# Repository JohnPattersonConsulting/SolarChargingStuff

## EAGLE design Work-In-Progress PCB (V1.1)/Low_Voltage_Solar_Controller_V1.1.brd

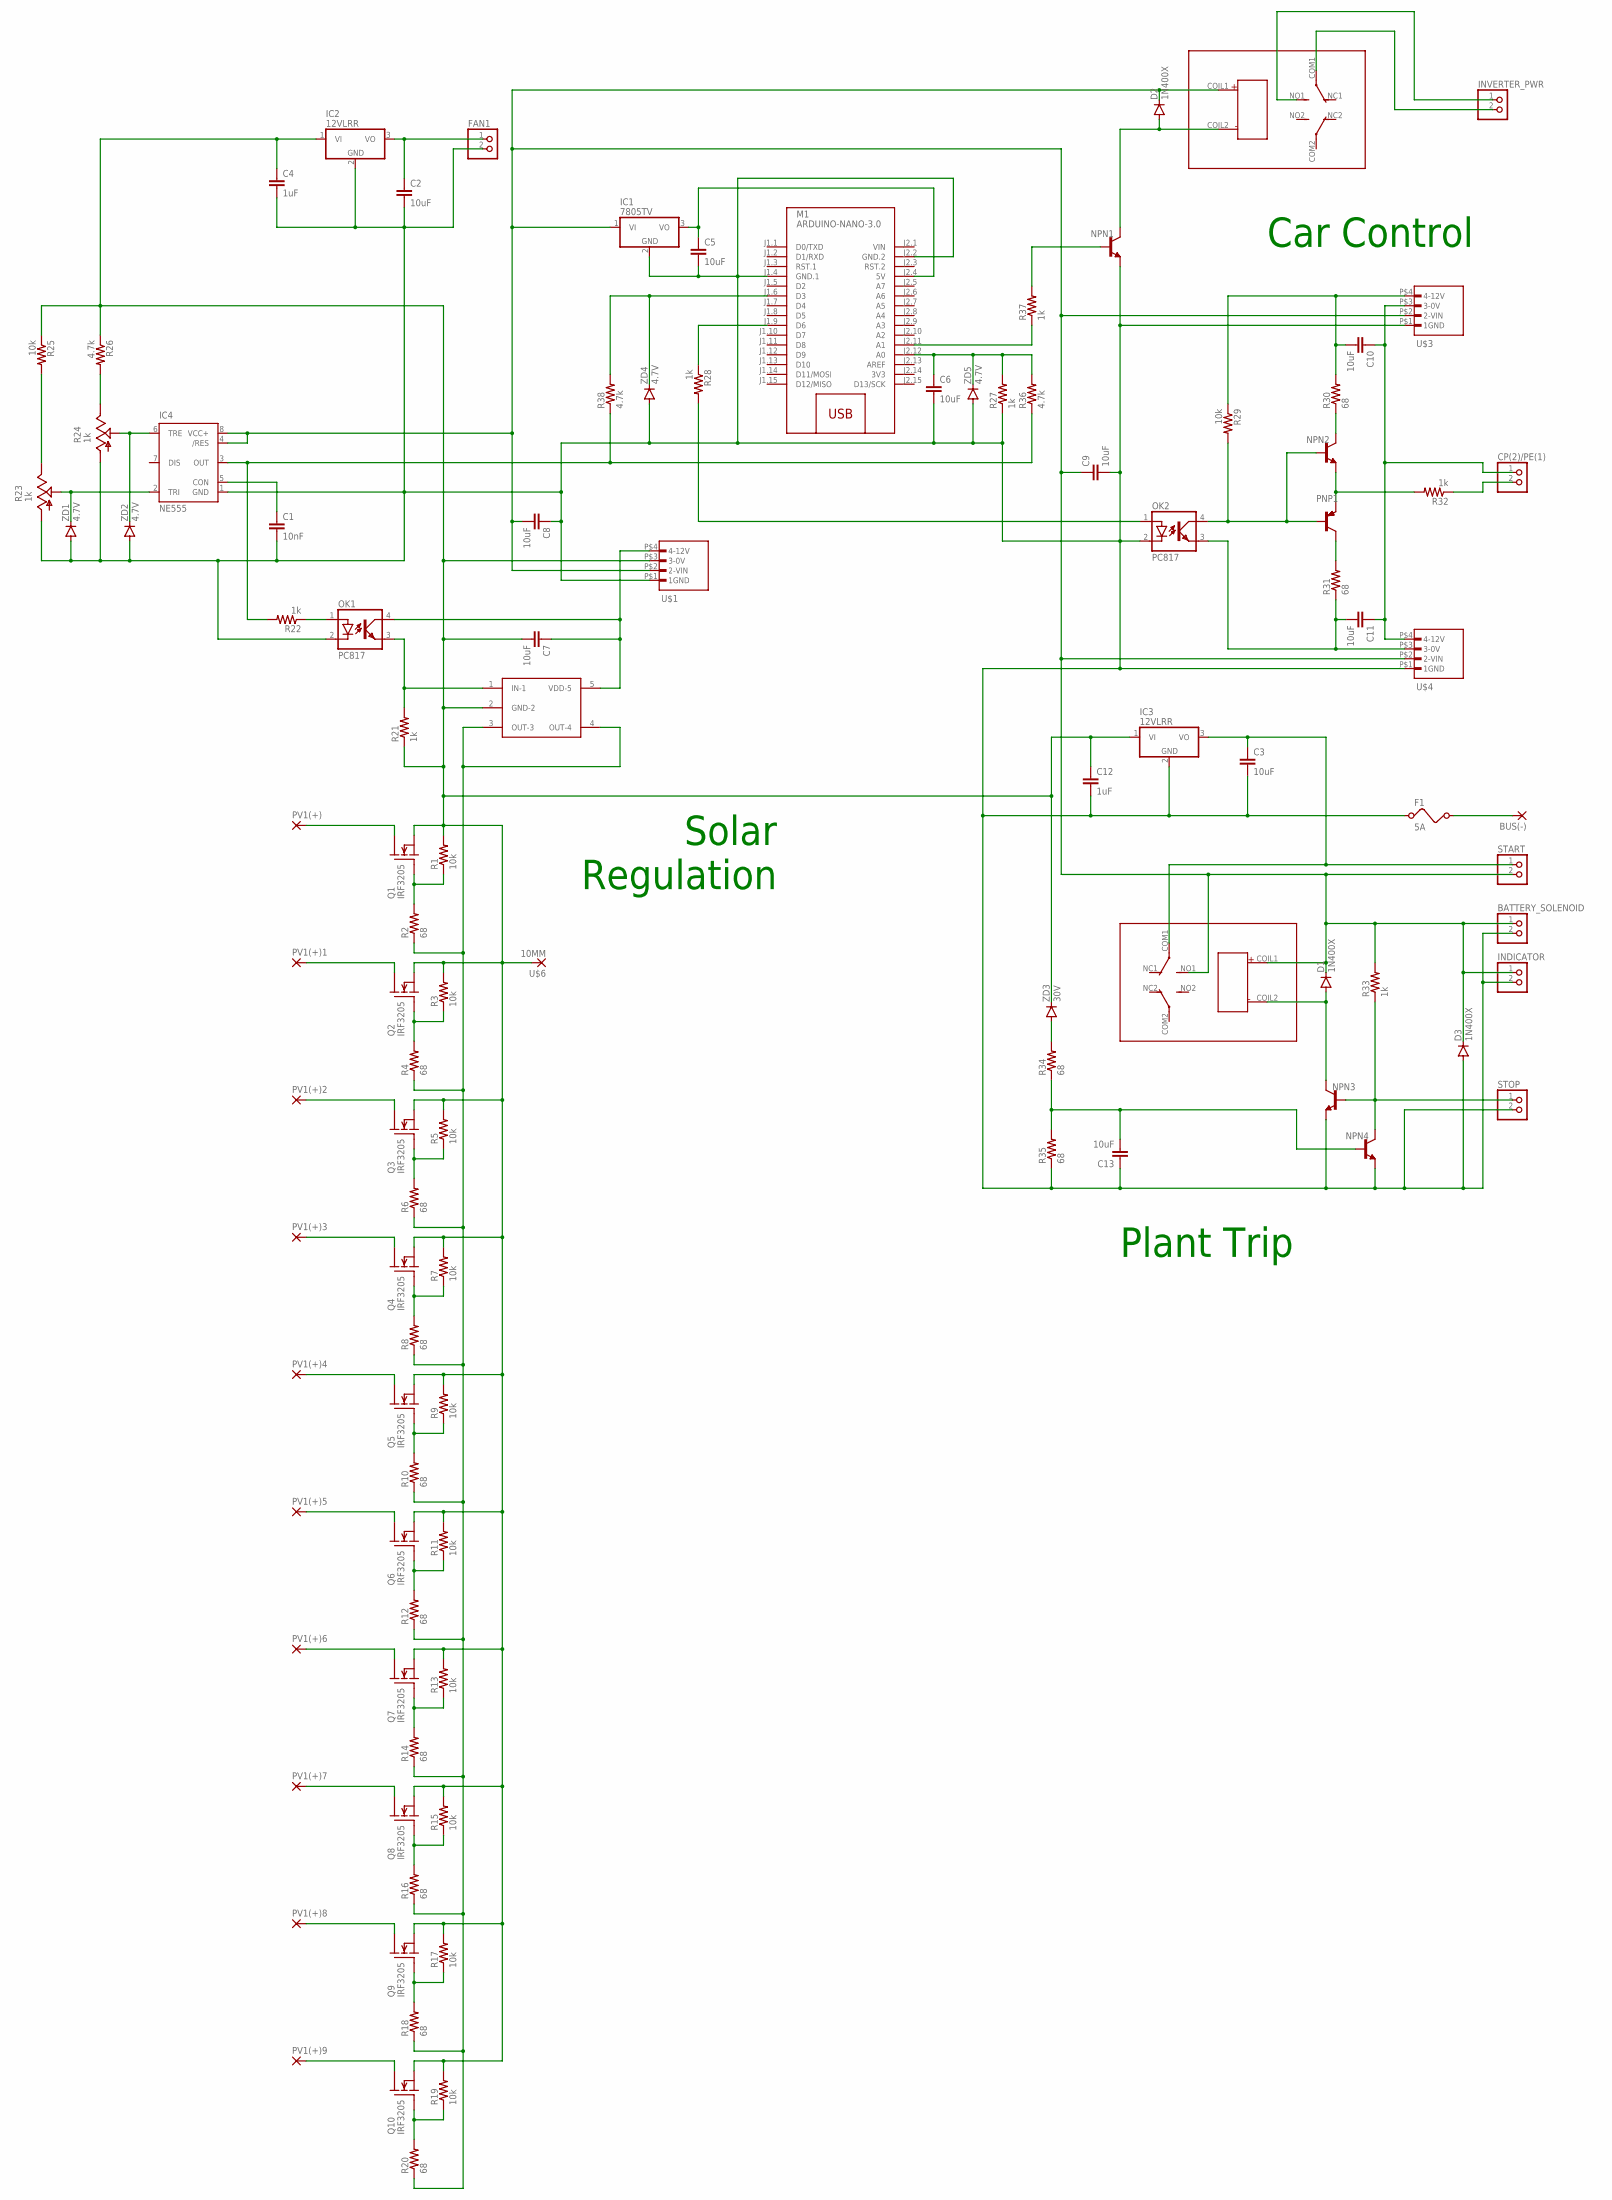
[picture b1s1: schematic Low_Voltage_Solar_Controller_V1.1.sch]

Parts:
BATTERY_SOLENOID: PINHD-1X2; 1X02
BUS(-): 5MM_PAD; 5MM
C1: 10nF; C0603
C2, C3, C5, C6, C7, C8, C9, C10, C11, C13: 10uF; C0805
C4, C12: 1uF; C0805
CP(2)/PE(1): PINHD-1X2; 1X02
D1, D2, D3: 1N400X; DO41-10
F1: 5A; FUSE_HOLDER
FAN1: PINHD-1X2; 1X02
IC1: 7805TV; TO220V
IC2, IC3: 12VLRR; TO220V
IC4: NE555; DIL-08
INDICATOR: PINHD-1X2; 1X02
INVERTER_PWR: PINHD-1X2; 1X02
M1: ARDUINO-NANO-3.0
NPN1, NPN2, NPN3, NPN4: -NPN-TO92-EBC; TO92-EBC
OK1, OK2: PC817; DIL04
PNP1: BCX58-PNP-TO92-EBC; TO92-EBC
PV1(+), PV1(+)1, PV1(+)2, PV1(+)3, PV1(+)4, PV1(+)5, PV1(+)6, PV1(+)7, PV1(+)8, PV1(+)9: 5MM_PAD; 5MM
Q1, Q2, Q3, Q4, Q5, Q6, Q7, Q8, Q9, Q10: IRF3205; TO220
R1, R3, R5, R7, R9, R11, R13, R15, R17, R19, R25, R29: 10k; R0805
R2, R4, R6, R8, R10, R12, R14, R16, R18, R20, R30, R31, R34, R35: 68; R0805
R21, R22, R27, R28, R32, R33, R37: 1k; R0805
R23, R24: 1k; RJ9W
R26, R36, R38: 4.7k; R0805
START: PINHD-1X2; 1X02
STOP: PINHD-1X2; 1X02
U$1, U$3, U$4: IB0512S-W75R3
U$2: NCP51100; SOT23-5
U$5, U$8: J104D2C12VDC.20S
U$6: 10MM
ZD1, ZD2, ZD4, ZD5: 4.7V; SOD-123_MINI-SMA
ZD3: 30V; DO214AA

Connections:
3V3: M1.J2.14 (3V3)
unnamed: PV1(+).P$1, Q1.2 (D)
unnamed: C4.1, C7.2, C12.1, IC2.1 (VI), IC3.1 (VI), Q1.3 (S), Q2.3 (S), Q3.3 (S), Q4.3 (S), Q5.3 (S), Q6.3 (S), Q7.3 (S), Q8.3 (S), Q9.3 (S), Q10.3 (S), R1.2, R3.2, R5.2, R7.2, R9.2, R11.2, R13.2, R15.2, R17.2, R19.2, R21.1, R25.1, R26.1, U$1.P$3 (3-0V), U$2.2 (GND-2), U$6.P$1, ZD3.C
unnamed: Q1.1 (G), R1.1, R2.2
unnamed: PV1(+)1.P$1, Q2.2 (D)
unnamed: M1.J1.6 (D3), R38.2, ZD4.C
unnamed: Q2.1 (G), R3.1, R4.2
unnamed: PV1(+)2.P$1, Q3.2 (D)
unnamed: Q3.1 (G), R5.1, R6.2
unnamed: PV1(+)3.P$1, Q4.2 (D)
unnamed: C5.1, IC1.3 (VO), M1.J2.4 (5V)
unnamed: Q4.1 (G), R7.1, R8.2
unnamed: PV1(+)4.P$1, Q5.2 (D)
unnamed: Q5.1 (G), R9.1, R10.2
unnamed: PV1(+)5.P$1, Q6.2 (D)
unnamed: Q6.1 (G), R11.1, R12.2
unnamed: PV1(+)6.P$1, Q7.2 (D)
unnamed: Q7.1 (G), R13.1, R14.2
unnamed: PV1(+)7.P$1, Q8.2 (D)
unnamed: Q8.1 (G), R15.1, R16.2
unnamed: PV1(+)8.P$1, Q9.2 (D)
unnamed: Q9.1 (G), R17.1, R18.2
unnamed: PV1(+)9.P$1, Q10.2 (D)
unnamed: Q10.1 (G), R19.1, R20.2
unnamed: R2.1, R4.1, R6.1, R8.1, R10.1, R12.1, R14.1, R16.1, R18.1, R20.1, U$2.3 (OUT-3), U$2.4 (OUT-4)
unnamed: OK1.3 (EMIT), R21.2, U$2.1 (IN-1)
unnamed: C7.1, OK1.4 (COL), U$1.P$4 (4-12V), U$2.5 (VDD-5)
unnamed: BATTERY_SOLENOID.1, C8.2, C9.1, D1.C, D2.C, D3.C, IC1.1 (VI), IC4.4 (/RES), IC4.8 (VCC+), INDICATOR.1, R33.2, START.2, U$1.P$2 (2-VIN), U$3.P$2 (2-VIN), U$4.P$2 (2-VIN), U$5.COIL1, U$8.COIL1, U$8.NO1
unnamed: OK1.1 (A), R22.1
unnamed: BATTERY_SOLENOID.2, C1.2, C2.2, C3.2, C4.2, C5.2, C6.2, C8.1, C9.2, C12.2, C13.1, D3.A, F1.P$1 (1), F1.P$2 (1), FAN1.2, IC1.2 (GND), IC2.2 (GND), IC3.2 (GND), IC4.1 (GND), INDICATOR.2, M1.J1.4 (GND.1), M1.J2.2 (GND.2), NPN1.E, NPN3.E, NPN4.E, OK1.2 (C), OK2.2 (C), R23.A, R24.A, R27.1, R35.1, STOP.2, U$1.P$1 (1GND), U$3.P$1 (1GND), U$4.P$1 (1GND), ZD1.A, ZD2.A, ZD4.A, ZD5.A
unnamed: C1.1, IC4.5 (CON)
unnamed: C2.1, FAN1.1, IC2.3 (VO)
unnamed: IC4.6 (TRE), R24.S, ZD2.C
unnamed: IC4.2 (TRI), R23.S, ZD1.C
unnamed: R23.E, R25.2
unnamed: R24.E, R26.2
unnamed: C6.1, M1.J2.12 (A0), R27.2, R36.2, ZD5.C
unnamed: M1.J1.9 (D6), R28.1
unnamed: OK2.1 (A), R28.2
unnamed: NPN2.B, OK2.4 (COL), PNP1.B, R29.2
unnamed: C10.1, C11.1, CP(2)/PE(1).1, U$3.P$3 (3-0V), U$4.P$4 (4-12V)
unnamed: C11.2, OK2.3 (EMIT), R31.1, U$4.P$3 (3-0V)
unnamed: C10.2, R29.1, R30.2, U$3.P$4 (4-12V)
unnamed: NPN2.E, PNP1.E, R32.2
unnamed: PNP1.C, R31.2
unnamed: NPN2.C, R30.1
unnamed: CP(2)/PE(1).2, R32.1
unnamed: BUS(-).P$1, F1.P$3 (2), F1.P$4 (2)
unnamed: D1.A, NPN3.C, U$8.COIL2
unnamed: NPN3.B, NPN4.C, R33.1, STOP.1
unnamed: C13.2, NPN4.B, R34.1, R35.2
unnamed: R34.2, ZD3.A
unnamed: C3.1, IC3.3 (VO), START.1, U$8.COM1
unnamed: M1.J2.11 (A1), R37.1
unnamed: IC4.3 (OUT), R22.2, R36.1, R38.1
unnamed: NPN1.B, R37.2
unnamed: D2.A, NPN1.C, U$5.COIL2
unnamed: INVERTER_PWR.2, U$5.COM1
unnamed: INVERTER_PWR.1, U$5.NO1
VIN: M1.J2.1 (VIN)

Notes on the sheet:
Car Control
Solar Regulation
Plant Trip

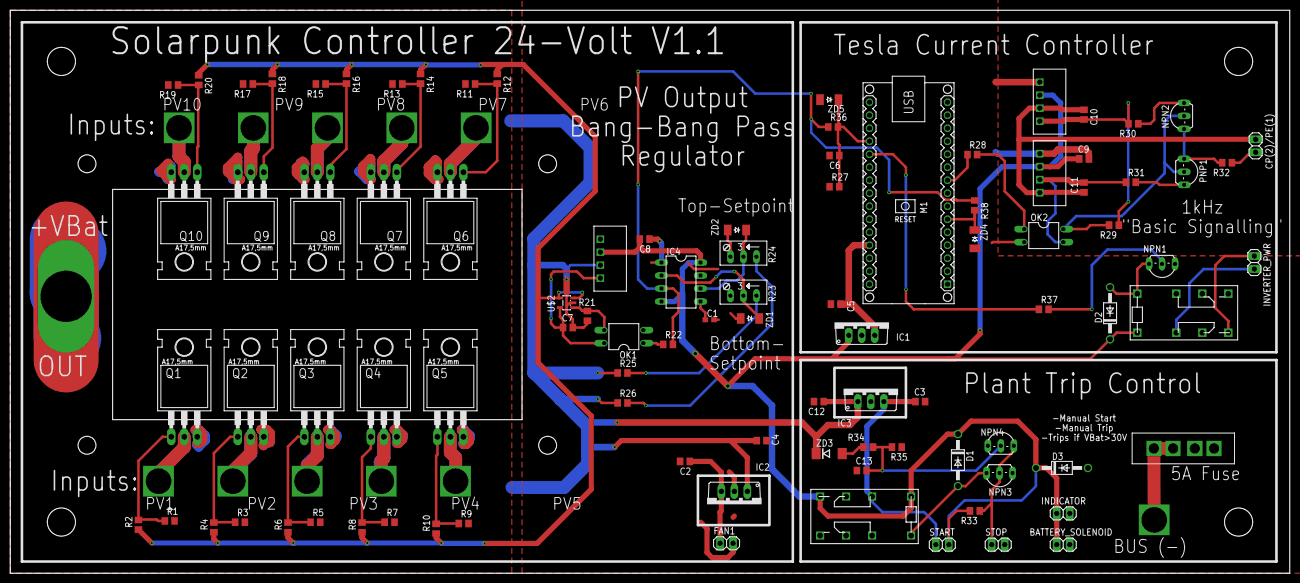
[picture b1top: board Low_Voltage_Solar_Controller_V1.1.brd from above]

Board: 2 copper layers, 250.0 x 110.0 mm, 107 parts (0 on the bottom side), 58 nets.

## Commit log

2024-05-12 Added work-in-progress PCB files and BS control Arduino sketch.

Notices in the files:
parts and their libraries:
diy-modules: Released under the Creative Commons Attribution 4.0 International License: http://creativecommons.org/licenses/by/4.0
